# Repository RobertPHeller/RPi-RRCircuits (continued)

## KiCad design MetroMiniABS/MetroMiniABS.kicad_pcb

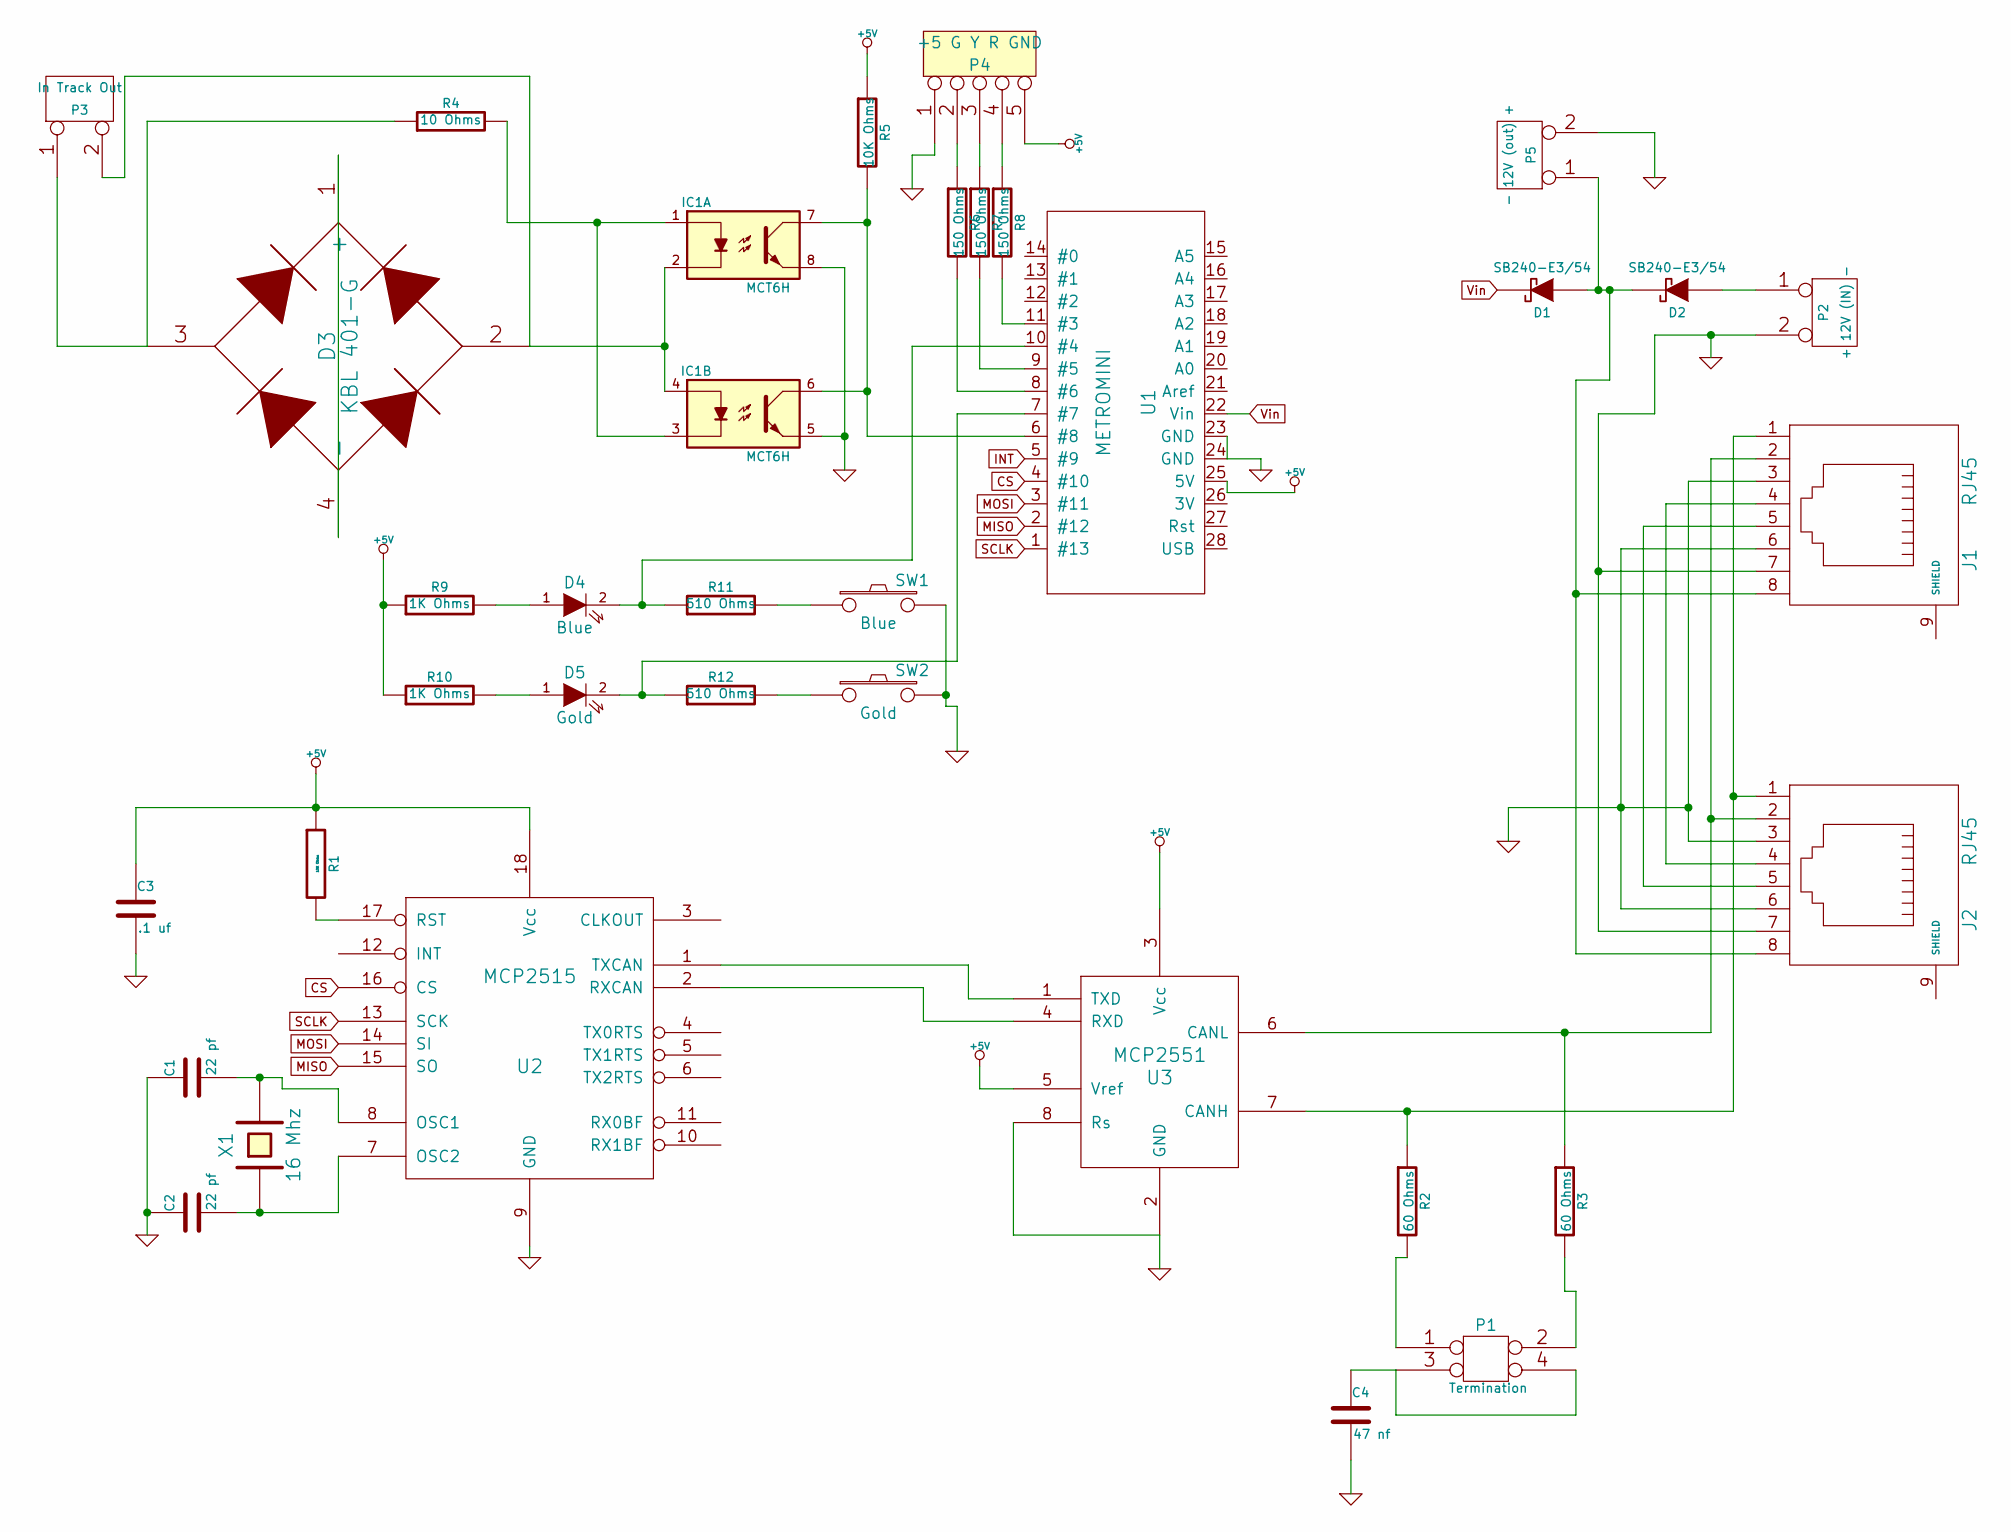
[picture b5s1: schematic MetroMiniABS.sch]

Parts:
C1, C2: 22 pf; Mouser Part Number 581-SR151A220KAR
C3: .1 uf; Mouser Part Number 21RZ310-RC
C4: 47 nf; Mouser Part Number 75-1C10Z5U473M050B
D1, D2: SB240-E3/54; Mouser Part Number 625-SB240-E3
D3: KBL 401-G; Mouser Part Number 750-KBL401-G
D4: Blue; Mouser Part Number 859-LTL17KTBS3KS
D5: Gold; Mouser Part Number 859-LTL-4251N
IC1: MCT6H; DIP-8__300; Mouser Part Number 782-MCT6H
J1, J2: RJ45; Mouser Part Number 710-615008144221
P1: Termination; Mouser Part Number 855-M20-9980246
P2: + 12V (IN) -; Mouser Part Number 710-691249510002
P3: In Track Out; Mouser Part Number 710-691249510002
P4: +5 G Y R GND; Mouser Part Number 782-MCT6H
P5: - 12V (out) +; Mouser Part Number 782-MCT6H
R1: 10K Ohms; Mouser Part Number 660-MF1/4LCT52R103J
R2, R3: 60 Ohms; Mouser Part Number 71-RN60C60R0B/R
R4: 10 Ohms; Mouser Part Number 782-MCT6H
R5: 10K Ohms; Mouser Part Number 782-MCT6H
R6, R7, R8: 150 Ohms; Mouser Part Number 782-MCT6H
R9, R10: 1K Ohms; Mouser Part Number 660-MF1/4LCT52R102J
R11, R12: 510 Ohms; Mouser Part Number 660-MF1/4LCT52R511J
SW1: Blue; Mouser Part Number 506-FSM4JH
SW2: Gold; Mouser Part Number 506-FSM4JH
U1: METROMINI
U2: MCP2515; DIL-18_300; Mouser Part Number 579-MCP2515-I/P
U3: MCP2551; DIL-8_300; Mouser Part Number 579-MCP2551-I/P
X1: 16 Mhz; Mouser Part Number 449-LFXTAL027945BULK

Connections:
+5V: C3.1, P4.5, R1.1, R5.1, R9.1, R10.1, U1.25 (5V), U2.18 (Vcc), U3.3 (Vcc), U3.5 (Vref)
CS: U1.4 (#10), U2.16 (CS)
GND: C1.1, C2.1, C3.2, C4.2, IC1.5, IC1.8, J1.3, J1.6, J1.7, J2.3, J2.6, J2.7, P2.2 (PM), P4.1, P5.2 (PM), SW1.2, SW2.2, U1.23 (GND), U1.24 (GND), U2.9 (GND), U3.2 (GND), U3.8 (Rs)
MISO: U1.2 (#12), U2.15 (SO)
MOSI: U1.3 (#11), U2.14 (SI)
unnamed: D3.1 (+), D3.4 (-)
unnamed: D3.3, P3.1, R4.1
unnamed: IC1.6, IC1.7, R5.2, U1.6 (#8)
unnamed: IC1.1, IC1.3, R4.2
unnamed: D3.2, IC1.2, IC1.4, P3.2 (PM)
unnamed: C4.1, P1.3, P1.4
unnamed: P1.2, R3.2
unnamed: P1.1, R2.2
unnamed: J1.1, J2.1, R2.1, U3.7 (CANH)
unnamed: J1.2, J2.2, R3.1, U3.6 (CANL)
unnamed: R12.2, SW2.1
unnamed: R11.2, SW1.1
unnamed: D5.1 (A), R10.2
unnamed: D4.1 (A), R9.2
unnamed: D4.2 (K), R11.1, U1.10 (#4)
unnamed: D5.2 (K), R12.1, U1.7 (#7)
unnamed: P4.4, R8.1
unnamed: P4.3, R7.1
unnamed: P4.2, R6.1
unnamed: R6.2, U1.8 (#6)
unnamed: R7.2, U1.9 (#5)
unnamed: R8.2, U1.11 (#3)
unnamed: U2.2 (RXCAN), U3.4 (RXD)
unnamed: U2.1 (TXCAN), U3.1 (TXD)
unnamed: C1.2, U2.8 (OSC1), X1.2
unnamed: C2.2, U2.7 (OSC2), X1.1
unnamed: R1.2, U2.17 (RST)
unnamed: D2.1 (A), P2.1
unnamed: D1.1 (A), D2.2 (K), J1.8, J2.8, P5.1
unnamed: J1.5, J2.5
unnamed: J1.4, J2.4
SCLK: U1.1 (#13), U2.13 (SCK)
Vin: D1.2 (K), U1.22 (Vin)

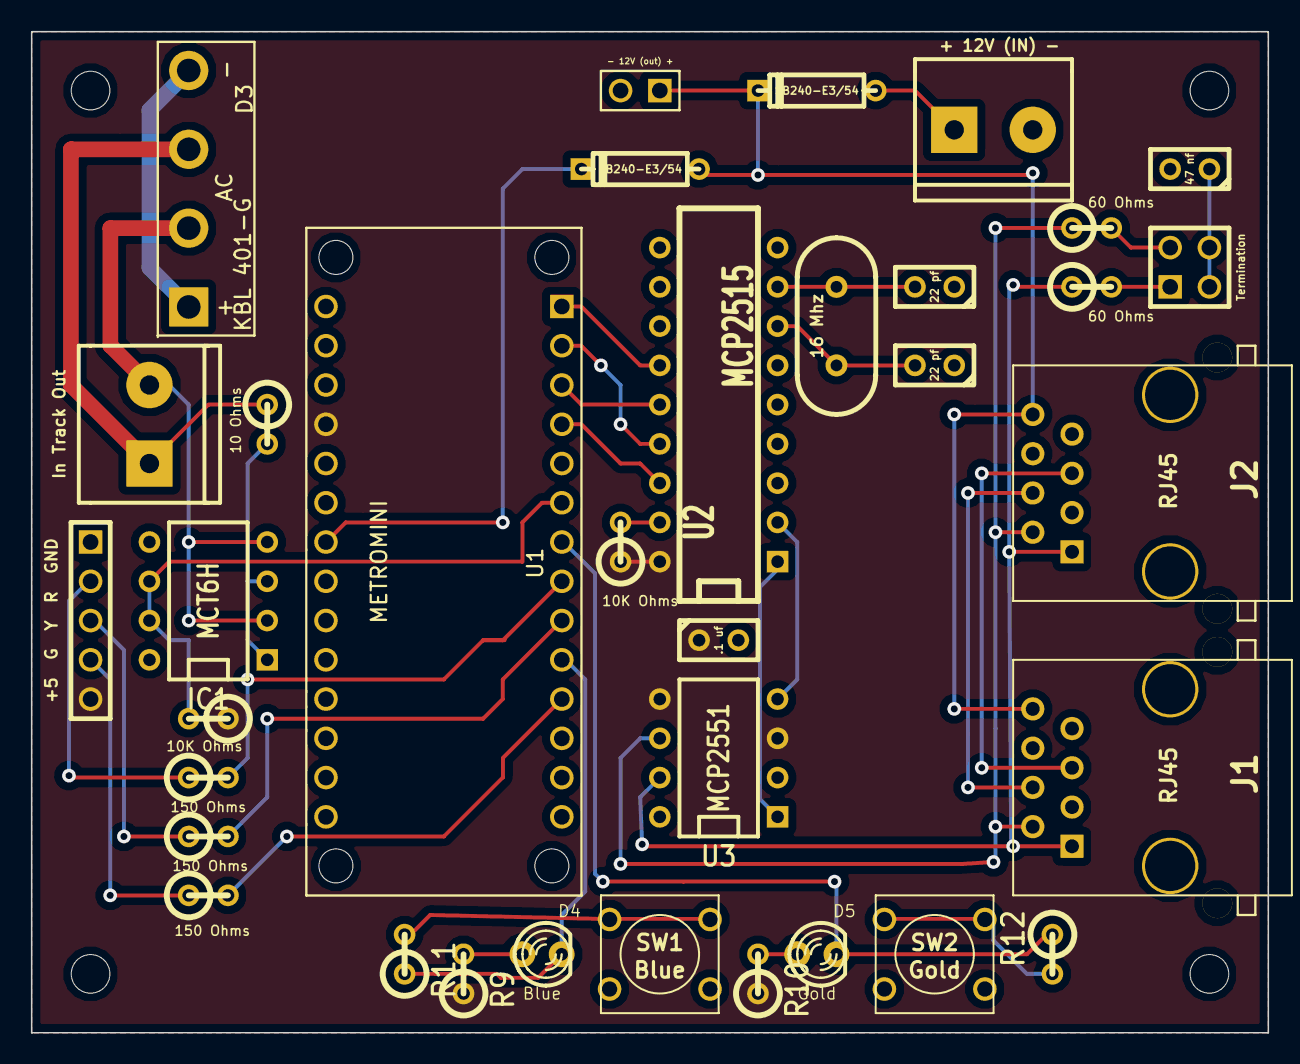
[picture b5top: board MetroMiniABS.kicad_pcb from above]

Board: 2 copper layers, 80.0 x 64.8 mm, 39 parts (0 on the bottom side), 38 nets.

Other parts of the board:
MH: MountingHole_2-5mm_RevA_Date21Jun2010
MH#2, MH#3, MH#4: MountingHole_2-5mm_RevA_Date21Jun2010
